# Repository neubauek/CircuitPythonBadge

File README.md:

# CircuitPythonBadge
Open Source Hardware Circuit Python Badge

https://kevinneubauer.com/portfolio/circuitpython-badge/

Known Issue(s):
V1.2:
- The VDD pin on the PAM8301 chip is missing a 1 uF and a 10 uF decoupling capacitor. Without these, the speaker audio will randomly drop out. Fixed in v1.3.

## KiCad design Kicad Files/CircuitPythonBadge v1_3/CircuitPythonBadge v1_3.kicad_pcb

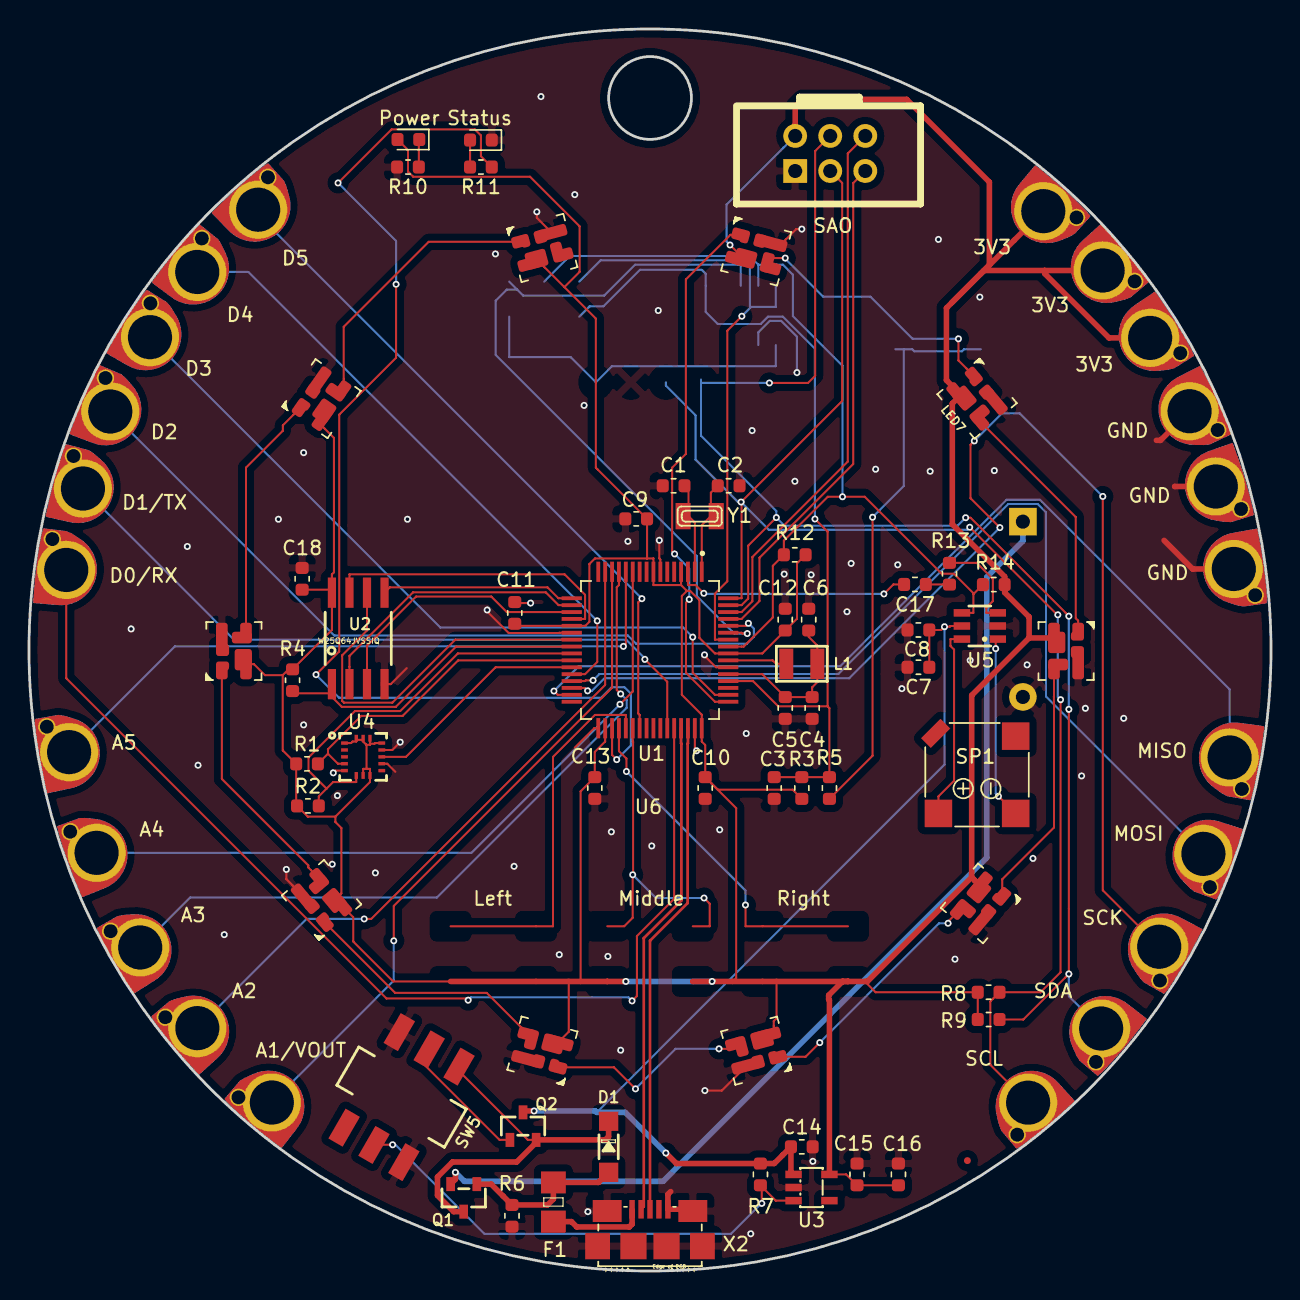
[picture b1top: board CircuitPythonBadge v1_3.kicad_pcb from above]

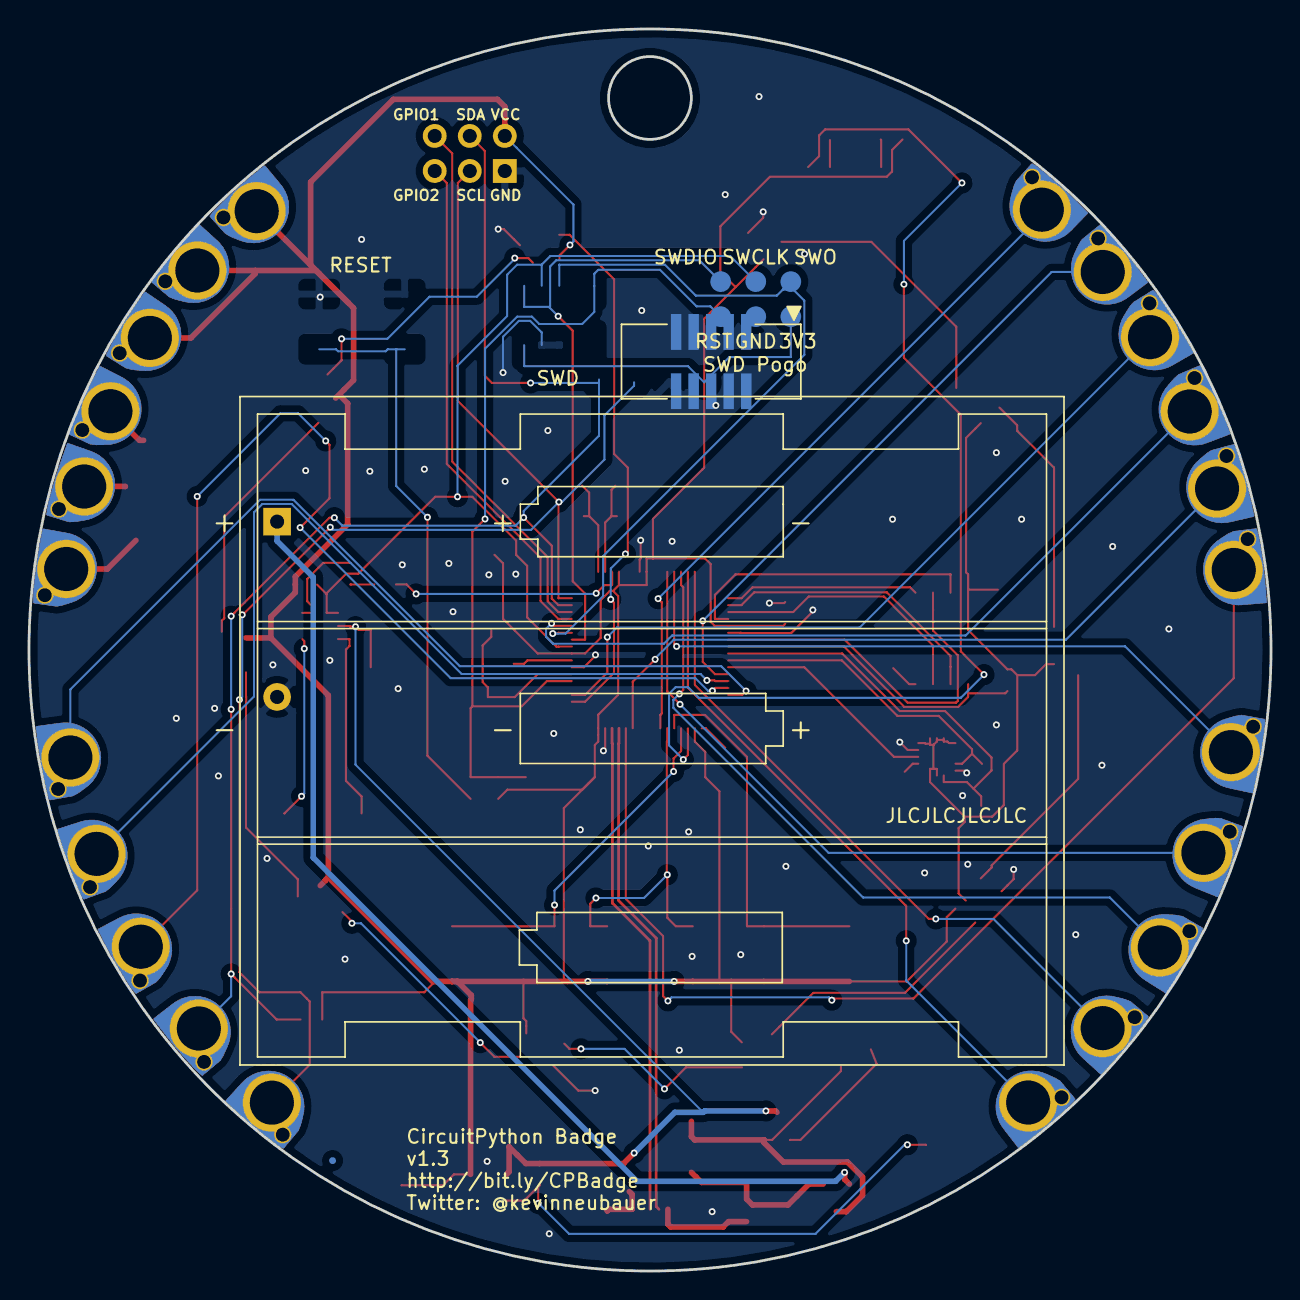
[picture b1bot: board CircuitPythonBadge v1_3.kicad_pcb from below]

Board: 2 copper layers, 90.0 x 90.0 mm, 86 parts (3 on the bottom side), 64 nets.

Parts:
BT1: Battery; BatteryHolder_Keystone_2464_3xAA
C1, C2: 13pF; C_0603_1608Metric
C3, C4, C9, C10, C11, C12, C13, C17, C18: 0.1uF; C_0603_1608Metric
C5, C7, C16: 1uF; C_0603_1608Metric
C6, C8, C14, C15: 10uF; C_0603_1608Metric
D1: MBR120; Adafruit Hallowing M0 Express-MICROBUILDER_SOD-123
F1: 5V-500mA; Adafruit Metro M4 Express-ADAFRUIT_R1206
FID1, FID2: Fiducial; Fiducial_0.5mm_Mask1.5mm
J1, J2, J3, J4, J5, J6, J8, J9, J10, J11, J12, J13, J14, J15, J16, J17, J18, J19, J21, J22, J24, J25: Conn_01x01; SewTapSolder
J23: SWD_Pads; Pogo SWD
L1: 10uH; Adafruit Metro M4 Express-MICROBUILDER_INDUCTOR_1007
LED1: RED; LED_0603_1608Metric
LED4: GREEN; LED_0603_1608Metric
LED5, LED6, LED7, LED8, LED9, LED10, LED11, LED12, LED13, LED14: SK6812; SK6812_Mini
Q1, Q2: DMG341; Adafruit Hallowing M0 Express-MICROBUILDER_SOT23-R
R1, R2, R3, R4, R8, R9, R14: 10K; R_0603_1608Metric
R5: 330; R_0603_1608Metric
R6, R7: 100K; R_0603_1608Metric
R10, R11, R12: 1K; R_0603_1608Metric
R13: 47K; R_0603_1608Metric
SP1: ST-025BT; BUZZER_SMT_7.5MM
SW5: JS202011SCQN; Adafruit Hallowing M0 Express-MICROBUILDER_DPDT_SMT_JS20201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
U1: ATSAMD51J19A-AU; QFP50P1200X1200X120-64N
U2: W25Q64JVSSIQ; SOIC8_208MIL
U3: AP2112K-3.3; Adafruit Metro M4 Express-SMARTPRJ_SOT23-DBV
U4: LIS3DHTR; Adafruit Circuit Playground Express-MICROBUILDER_LGA16_3X3MM
U5: PAM8301; Adafruit Circuit Playground Express-MICROBUILDER_SOT23-6
U6: SH1106_1.3; SH1106_1.3_I2C_128x64
X2: 10118192-0001LF; 10118192-0001LF(MICRO-USB-B-AMPHENOL-FCI)
X3: Badgelife_sao_connector_v169bis; Badgelife-SAOv169-BADGE-2x3
Y1: FC-135 32.7680KA-A5; Adafruit Metro M4 Express-ADAFRUIT2_XTAL3215

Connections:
+3V3: C9.1, C10.2, C11.1, C12.2, C13.1, C15.1, C16.1, C18.1, J16.1, J17.1, J21.1, J23.1, LED4.2, LED5.4, LED6.4, LED7.4, LED8.4, LED9.4, LED10.4, LED11.4, LED12.4, LED13.4, LED14.4, R1.1, R2.1, R3.1, R4.1, R8.1, R9.1, R12.1, R14.1, U1.4, U1.8, U1.21, U1.34, U1.48, U1.56, U2.8, U3.5, U4.1, U4.7, U4.8, U4.13, U4.14, U4.15, U4.16, U6.1, X3.1
/A0_SPEAKER: C17.2, U1.3
/A1: J11.1, U1.14
/A2: J12.1, U1.15
/A3: J13.1, U1.13
/A4: J14.1, U1.11
/A5: J15.1, U1.12
/D0_RX: J1.1, U1.44
/D1_TX: J2.1, U1.43
/D2: J3.1, U1.60
/D3: J4.1, U1.50
/D4: J5.1, U1.28
/D5: J6.1, U1.39
/D7_LIS_IRQ: U1.27, U4.11
/D8_LIS_SCL: R1.2, U1.26, U4.4
/D9_LIS_SDA: R2.2, U1.25, U4.6
/D13_LED: R11.1, U1.35
/D+: U1.46, X2.D+
/D-: U1.45, X2.D-
/EN: R7.1, SW5.P$2, U3.3
/FLASH_CS: R4.2, U1.24, U2.1
/FLASH_IO0: U1.17, U2.5
/FLASH_IO1: U1.18, U2.2
/FLASH_IO2: U1.19, U2.3
/FLASH_IO3: U1.20, U2.7
/FLASH_SCK: U1.23, U2.6
/MISO: J9.1, U1.31
/MOSI: J8.1, U1.29
/NEOPIX: LED5.3, U1.49
/ON-OFF: Q2.1, SW5.P$5
/RESET: C3.1, J23.3, R3.2, R5.1, U1.52, U6.10
/SAO_GPIO1: U1.62, X3.5
/SAO_GPIO2: U1.61, X3.6
/SCK: J10.1, U1.30
/SCL: J24.1, R8.2, U1.64, X3.4
/SDA: J25.1, R9.2, U1.63, X3.3
/SWCLK-SPK_SD: J23.5, R12.2, R14.2, U1.57, U5.4, U6.4
/SWDIO: J23.6, U1.58, U6.2
/SWO: J23.4, U1.59, U6.6
GND: BT1.2, C1.1, C2.1, C3.2, C4.2, C5.2, C6.2, C7.2, C8.1, C9.2, C10.1, C11.2, C12.1, C13.2, C14.2, C15.2, C16.2, C18.2, J18.1, J19.1, J22.1, J23.2, LED1.1, LED5.2, LED6.2, LED7.2, LED8.2, LED9.2, LED10.2, LED11.2, LED12.2, LED13.2, LED14.2, R6.2, R10.2, SW5.P$3, SW5.P$6, U1.7, U1.22, U1.33, U1.47, U1.54, U2.4, U3.2, U4.5, U4.10, U4.12, U5.2, U6.3, U6.5, X2.CGND, X2.GND, X3.2
unnamed: C1.2, U1.2, Y1.P$1
unnamed: C2.2, U1.1, Y1.P$2
unnamed: C4.1, C5.1, C6.1, L1.P$1, U1.53
unnamed: C17.1, R13.1
unnamed: D1.C, Q1.3, Q2.2, SW5.P$4
unnamed: F1.1, X2.VBUS
unnamed: L1.P$2, U1.55
unnamed: LED1.2, R11.2
unnamed: LED4.1, R10.1
unnamed: LED5.1, LED7.3
unnamed: LED6.1, LED8.3
unnamed: LED7.1, LED9.3
unnamed: LED10.1, LED12.3
unnamed: LED8.1, LED10.3
unnamed: LED11.1, LED13.3
unnamed: LED9.1, LED11.3
unnamed: LED12.1, LED14.3
unnamed: LED6.3, LED13.1
unnamed: R13.2, U5.3
unnamed: SP1.+, U5.6
unnamed: SP1.-, U5.1
V+: C7.1, C8.2, C14.1, Q2.3, R7.2, U3.1, U5.5
VBAT: BT1.1, Q1.2
VBUS: D1.A, F1.2, Q1.1, R6.1

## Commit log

2019-11-04 Updated Readme with Image
2019-11-04 Added firmware and bootloader files
2019-12-02 Uploaded v1.3 of design
    Fixed issue with missing decoupling caps for PAM8301
    Used a new footprint for SK6812 LEDS
